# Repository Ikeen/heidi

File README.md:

# heidi 
GPS tracking system for alpine pasture - or simply sheeps :-)

## Table of contents
* [Licence info](#licence-info)
* [Project](#project)
* [Milestones](#milestones)
* [Solutions](#solutions)
* [News](#news)

## Licence info

You may freely use or copy this project under the following conditions:

* non-commercial use
* no warranties
	
## Project

The project goal:

* creating a tracker system from scratch
* using free available cheap standard electronic components
* 3D printable housings
* with in situ solar power generation for continuous operation
* vitality monitoring
* local LoRa network with client tracker modules for individual animal monitoring
	
## Milestones

* functional prototype - done
* CAD work for housings - done 
* initial web service - done
* 1st gateway tracker module for testings - done
* endurance tests for housing, power supply and modul reliability - done
* 1st client tracker module for testings - done
* endurance tests for lokal LoRa netwok reliability (gateway tracker <-> client trackers) - done
* accelerometer for vitality monitoring - done
* geofencing functionality - done
* store configuration data into flash memory - tbd
* tool for programming configuration data into flash memory - tbd

## Solutions

some solutions to various problems

* sending data via GSM cause Arduino to crash: Try another orientation of GSM-antenna. Sometimes a piece of copper acts like a receiving antenna, what may have an impact on the Arduino board.
* sending / getting data via GSM is unreliable: Check power connection to battery, MOSFET, DC-DC-Converter - they should be strong. In my case I soldered wires directly to IC-pins.
* serial communication between components produces strange characters: internally pullup RX-wire with "pinMode(_RXD, INPUT_PULLUP);". The HardwareSerial library seems not to do that. Most time it works without dedicated pullup - sometimes it doesn't.
* never place GSM-antenna and DC-DC-converter near by together

## News

* after various problems with communication reliability - especially with low battery - we find out, that placing a additional big capacitor on the power input of the DC-DC-converter, solves a buck of problems. It seems we can even omit the backup battery when we do so - but the DC-DC-converter is still needed. The SIM800L module will not work properly with less then 3.8V - even if the manual tells: it will.
* the fixing via belt clip turned out to be not reliable. We went back to the first intended fixing by screwing the hard plastic parts directly to a belt. Description and pictures coming soon on this channel.
* the buffer battery on the GPS module empties within a few days due to the way we use it. Let me explain a little more: keep the GPS module in power save tracking mode will give us quick results (saving time saves power) but it still draws about 10mA, way too much - so we completely cut it off from power. Usually the buffer battery enables the module to backup some information about the last position lock. These information eases and speeds up the next position lock. Unfortunately the battery is weak and its charging to slow, so it will be discharged after a couple of days. Removing the Battery from module and connecting the backup-pin of the UBLOX to 3.3V from Arduino will solve that problem and we will significantly profit from the backup function. The backup draws about 15uA - no problem. Assembly instructions and sketches will be updated soon. (done)
* the battery solar charging modules in Heidi hardware version 1 and 2 have one or two small big problems: if they are, for what reason ever, shortly disconnected from battery, sometimes they may be unable to reconnect the load to the battery. Furthermore their thresholds of hysteresis (deep discharge protection) are too low, so if the voltage goes too low ESP32 will boot in a circle until the modules cut off from load due to under voltage. So far so good, but in case of recharged batteries they will reconnect the load too early, so the ESP32 will directly starts with booting in a circle until the voltage is too low again. We've decided to implement a own protection circuit which cuts off on 2.7V and reconnects on 3.0V. That will keep the ESP32 in save states. Additionally that means, we can use Modules without under voltage protection. BUT: Doing this we loose short circuit protection too. We strongly recommend batteries with included protection PCB. (no barbecue on pasture!)

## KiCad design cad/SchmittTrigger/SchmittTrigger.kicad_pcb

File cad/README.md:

# heidi - cad
Some CAD- and 3D-printing hints

## Table of contents
* [CAD](#cad)
* [3D-printing](#3d-printing)
  * [Printing direction](#printing-direction)
  * [Dealing with ASA-filament](#dealing-with-asa-filament)
  * [Warping](#warping)
  * [Solutions](#solutions)
  * [Notes](#notes)
* [Schmitt-Trigger](#schmitt-trigger)
  * [KiCad](#kicad)
  * [Get a PCB](#get-a-pcb)
  * [Electronic parts](#electronic-parts)

## CAD
All CAD was done with [FreeCad](https://www.freecad.org/). All CAD project files are uploaded too (*.fcstd).

## 3D-printing
For our purposes we decided to use 3D print for building up housings. This is flexible and cost efficient. For more reliability against weather and mechanical stress it would be better to use housings milled from the solid material. There are good offers for 3-axis CNC mills - maybe we will test this later on. (It seems we seriously need to talk to Santa regarding this. :-D )
### Printing direction
For mechanical reasons you need to consider printing direction. 3D printed objects do have less mechanical strength in vertical printing direction, so the orientation of objects during printing process matters. You may use the models or *.stl files with number 3 in the file name to get models already ready for printing. Most of them are doubled and connected by thin walls, to get a stable printing process.
### Dealing with ASA-filament
The outdoor usage of Heidi-Tracker requires a weather proofed housing material. We decided for ASA-filament from PolyMaker (for no special reasons). If you not own a industrial like 3D-printer, printing ASA-filament is not quite simple. The temperature for the material nozzle and the build plate (bed) needs to be adjusted depending on the geometry of the part you intend to print. (As far as we discovered due to many tries.)
### Warping
[(warping - see here)](https://support.ultimaker.com/hc/article_attachments/360009279100/How_to_fix_warping_Warping_model.jpg)<br />
Warping is the main issue while printing ASA filament. There are many hints you can find in the internet to fix warping. 

### Solutions
some solutions to various problems
* to minimize warping you may use a frame, like the one in the picture below, together with at least 20 brim lines. 

### Notes
* There are slightly different sizes of GPS-antenna boards used. Currently GPSAntennaClip is for the bigger one (28mm edge length), GPSAntennaClip3 is for the smaller one (25mm edge length) 

## Schmitt-Trigger
As mentioned in the introducing README, the cut-off threshold of the battery protection circuits (2.4 volts) is too low and leads heidi into a dead lock if the voltage goes below 2.6 volts. Therefore we decided to create a own protection circuit, which cuts off at about 2.8 volts and brings heidi back to power at about 3.1 volts. That ensures, that the ESP32 works correctly (when empowered). (By the way: It's our first own PCB - it was a huge fun to research, learn to calculate a Schmitt-Trigger, to test, to explore new CAD-software...)

Keep in mind: You nevertheless need a battery protection circuit. The Schmitt-Trigger will continously draw a small current too. We decided to use LiPo batteries with [included protection](https://www.trustfire.com/collections/batteries/).

### KiCad
The software we're using for schematics an PCB layout is [KiCad](https://www.kicad.org). You find the project files unter /SchmittTrigger. 

### Get a PCB
The PCB has just one layer and no throughplatings - even for the power connections, what saves costs. The gerber files, needed for ordering PCBs online, are in the zip file. We've ordered the PCB [here]( https://aisler.net) -  good price, quick service. 

### Electronic parts
Be sure to use a dual channel rail to rail operational amplifier with a minimum operation voltage of 2.7 volt. Keep an eye on its supply current - it should be less as possible. The P-channel FET is a power-FET, but maybe another will do too, because there are just a few milliamps to manage.

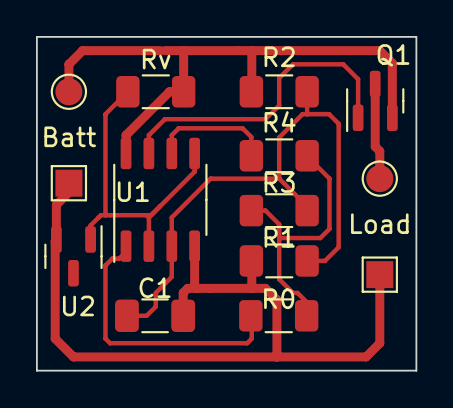
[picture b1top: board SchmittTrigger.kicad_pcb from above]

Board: 2 copper layers, 21.1 x 18.5 mm, 14 parts (0 on the bottom side), 9 nets.

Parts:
-1: Battery; TestPoint_Pad_1.5x1.5mm
Batt: +; TestPoint_Pad_D1.5mm
C1: 10µF; C_1206_3216Metric_Pad1.33x1.80mm_HandSolder
Load: +; TestPoint_Pad_D1.5mm
Load2: -; TestPoint_Pad_1.5x1.5mm
Q1: PMV32UP; SOT-23
R0: 0R; R_1206_3216Metric_Pad1.30x1.75mm_HandSolder
R1: 56k; R_1206_3216Metric_Pad1.30x1.75mm_HandSolder
R2: 82k; R_1206_3216Metric_Pad1.30x1.75mm_HandSolder
R3: 560k; R_1206_3216Metric_Pad1.30x1.75mm_HandSolder
R4: 100k; R_1206_3216Metric_Pad1.30x1.75mm_HandSolder
Rv: 22k; R_1206_3216Metric_Pad1.30x1.75mm_HandSolder
U1: TS912; SO-8_3.9x4.9mm_P1.27mm
U2: LM4041-N; SOT-23

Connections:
GND: -1.1, C1.2, Load2.1, R1.1, U1.4 (V-), U2.2 (A)
unnamed: Batt.1, Q1.2 (S), R2.2, Rv.1, U1.8 (V+)
unnamed: C1.1, R1.2, R2.1, R3.1, U1.3 (+)
unnamed: Load.1, Q1.3 (D)
unnamed: Q1.1 (G), U1.7
unnamed: R0.1, R3.2, R4.2
unnamed: R0.2, U1.1
unnamed: R4.1, U1.6 (-)
unnamed: Rv.2, U1.2 (-), U1.5 (+), U2.1 (K)

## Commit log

2018-12-29 add frontend files
2018-12-29 rename files and add directory
2018-12-29 add a Readme file
2018-12-29 initial
2018-12-29 Delete .cproject
    clean up
2018-12-29 Delete heidi.cpp
    clean up
2018-12-29 Delete .project
    clean up
2018-12-29 test
2018-12-29 esp32
2018-12-29 pinout
2018-12-29 readme
2018-12-29 filter changes
2018-12-29 ESP daten hinzugefügt
2019-01-01 some doku
2019-03-13 erste GPS testversion
2019-03-13 add some Doku
2019-03-15 add small changes
2019-03-25 add picture as backgroundimage
2019-07-06 long term test
2020-06-02 initial power management
2020-06-02 add cad
2020-06-05 some cad corrections
2020-06-10 add assembly instructions
2020-06-18 update assembly instructions
2020-06-22 restructuring of code started
2020-06-22 fix data handling
2020-07-06 new GPRS behavior
2020-07-07 reenable GPRS
2020-10-08 some reorganizing
2020-11-06 initial geofencing added
2021-03-22 add accelerometer measurements and i2c switch
2021-03-23 change database structure add creating new fence
2021-03-23 remove old files
2021-03-24 use local time for selecting and view
2021-05-17 final version 2 with accelerometer
2021-05-17 remove circuit.pdf
2021-05-17 new database configuration
2021-05-20 fix alert state behavior
2021-05-25 final testing image V2
2021-05-25 improve web frontend / re-add push_settings / change password
2021-06-15 add power-management documentation
2021-10-14 some bugfixes
2021-10-14 remove .gitignore
2021-10-14 cleanup repository
2021-10-14 remove old files from repository
2021-11-05 upcoming new hardware
2021-11-12 remove TinyGSM library
2021-11-22 enable accelerometer during measuring
2021-11-22 wrong compiler switch
2021-12-30 bugfixes, initial config interface, RTC fast mem usage
2022-01-05 remove TinyGPS++ lib
2022-01-12 new positioning procedure / bugfixes
2022-01-12 gps bugfix
2022-01-22 add cad readme
2022-01-22 updat cad/readme.md
2022-01-22 test cad/readme.md
2022-01-26 bugfix/new show_data.phtml
2022-01-26 test flash settings
2022-01-26 bugfix on show_data.phtml
2022-01-30 fix serious problem with data handling
2022-02-02 add LoRa test code
2022-03-11 add AT6558 GPS chip support
2022-03-18 backend: add threadsave data access, frontend: check data before pushing it to database
2022-03-18 change getNextnDataSets, fix data access deadlock
2022-03-31 update cad files
2022-03-31 remove old cad files
2022-04-16 get V3 working
2022-04-21 new gasket design
2022-04-21 Delete .stl
    remove garbage
2022-04-21 halt ULP during GSM transmission / bugfixes
2022-04-22 won't comment that
2022-04-28 change solar plate to mid box
2022-05-23 add threshold for data requests
2022-05-24 add fake herd id
2022-05-30 change temperature measurement
2022-06-03 measure temp. twice
2022-06-09 change transmission mode
2022-07-07 V3.1
2022-08-23 add PCB, update docs
2022-08-23 update backend/README
2022-08-24 add heidi logo
2022-08-24 add images
